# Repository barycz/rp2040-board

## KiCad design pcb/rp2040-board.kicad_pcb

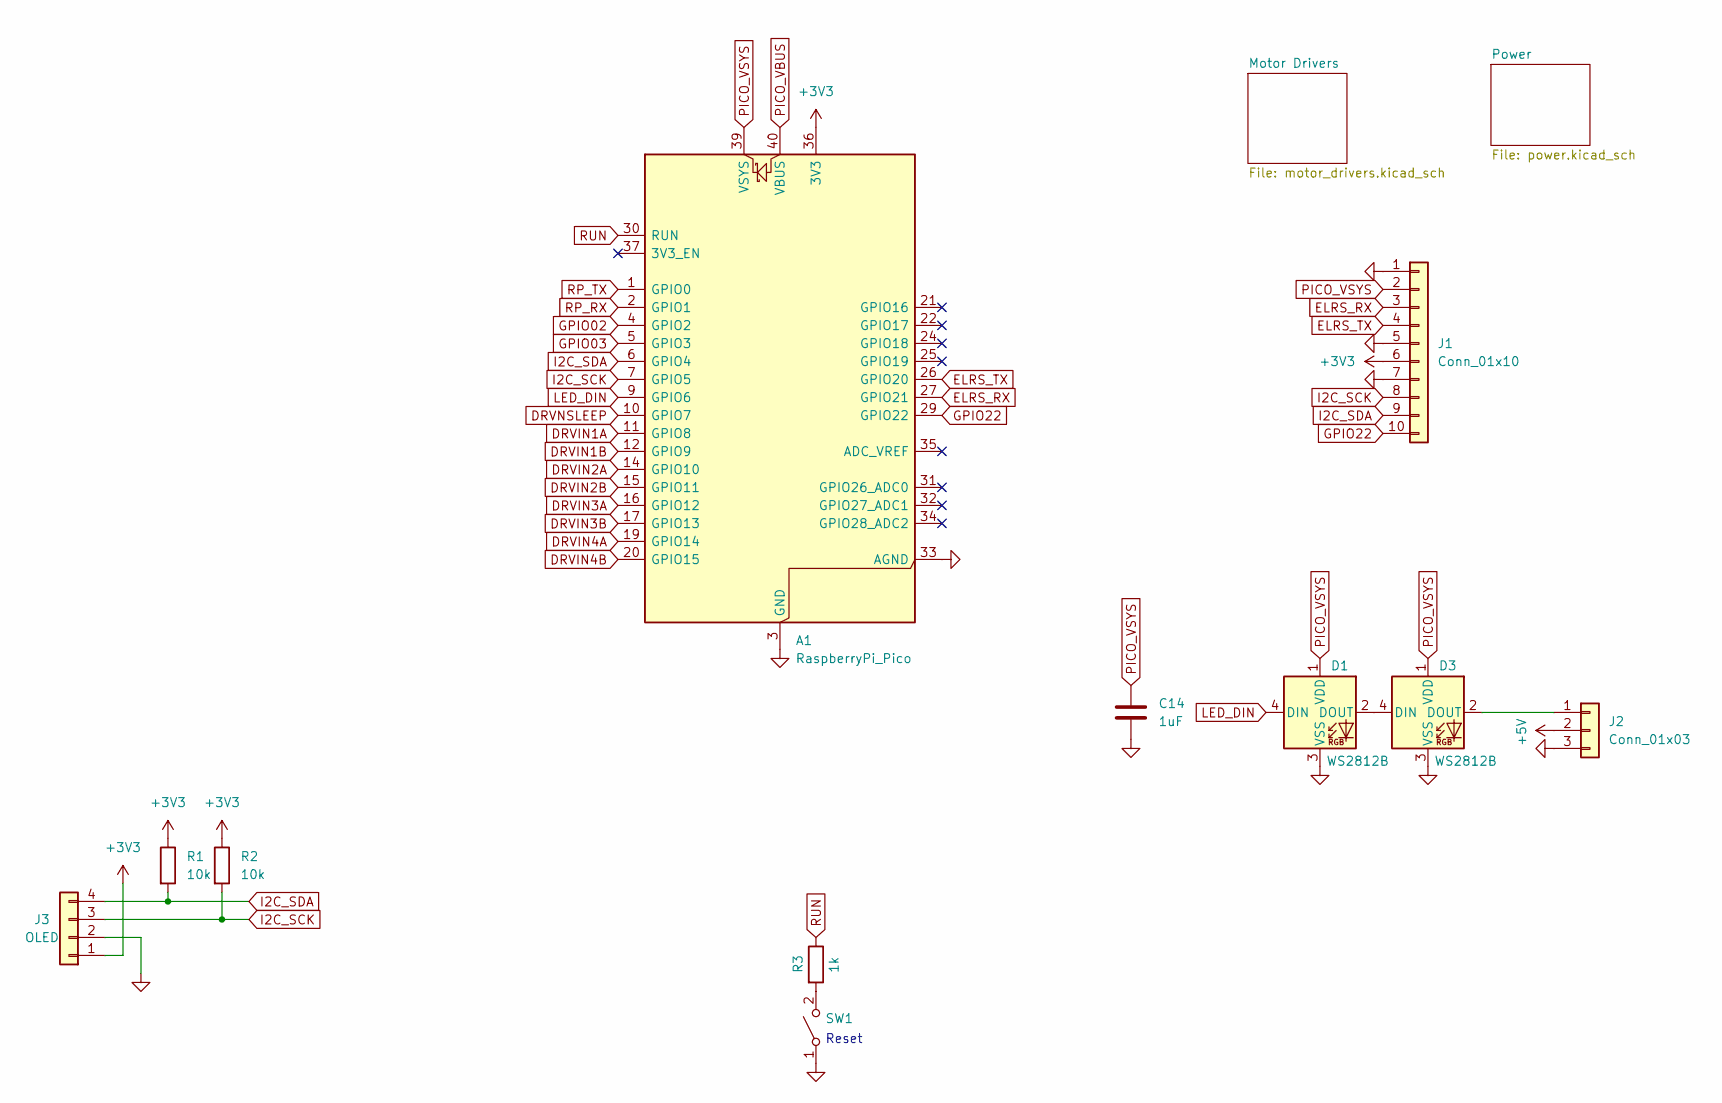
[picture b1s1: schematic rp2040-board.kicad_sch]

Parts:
A1: RaspberryPi_Pico; RaspberryPi_Pico_Common_SMD
C14: 1uF; C_0805_2012Metric; LCSC Part C28323
D1, D3: WS2812B; LED_WS2812B_PLCC4_5.0x5.0mm_P3.2mm; LCSC Part C42417498
J1: Conn_01x10; PinHeader_1x10_P2.54mm_Vertical
J2: Conn_01x03; PinHeader_1x03_P2.54mm_Vertical
J3: OLED; i2c oled display 0.96 inch VCC GND; JLCPCB BOM false
R1, R2: 10k; R_0402_1005Metric; LCSC Part C25744
R3: 1k; R_0402_1005Metric; LCSC Part C11702
SW1: TS-1187A-B-A-B; SW_Push_1P1T_XKB_TS-1187A; LCSC Part C318884

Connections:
+3V3: A1.36 (3V3), J1.6, J3.1, R1.1, R2.1; also elsewhere on the board
+5V: J2.2; also elsewhere on the board
DRVIN1A: A1.11 (GPIO8); also elsewhere on the board
DRVIN1B: A1.12 (GPIO9); also elsewhere on the board
DRVIN2A: A1.14 (GPIO10); also elsewhere on the board
DRVIN2B: A1.15 (GPIO11); also elsewhere on the board
DRVIN3A: A1.16 (GPIO12); also elsewhere on the board
DRVIN3B: A1.17 (GPIO13); also elsewhere on the board
DRVIN4A: A1.19 (GPIO14); also elsewhere on the board
DRVIN4B: A1.20 (GPIO15); also elsewhere on the board
DRVNSLEEP: A1.10 (GPIO7); also elsewhere on the board
ELRS_RX: A1.27 (GPIO21), J1.3
ELRS_TX: A1.26 (GPIO20), J1.4
GND: A1.3 (GND), A1.8 (GND), A1.13 (GND), A1.18 (GND), A1.23 (GND), A1.28 (GND), A1.33 (AGND), A1.38 (GND), C14.2, D1.3 (VSS), D3.3 (VSS), J1.1, J1.5, J1.7, J2.3, J3.2, SW1.1 (A); also elsewhere on the board
GPIO02: A1.4 (GPIO2); also elsewhere on the board
GPIO03: A1.5 (GPIO3); also elsewhere on the board
GPIO22: A1.29 (GPIO22), J1.10
I2C_SCK: A1.7 (GPIO5), J1.8, J3.3, R2.2; also elsewhere on the board
I2C_SDA: A1.6 (GPIO4), J1.9, J3.4, R1.2; also elsewhere on the board
LED_DIN: A1.9 (GPIO6), D1.4 (DIN)
unnamed: D1.2 (DOUT), D3.4 (DIN)
unnamed: D3.2 (DOUT), J2.1
unnamed: R3.2, SW1.2 (B)
PICO_VBUS: A1.40 (VBUS); also elsewhere on the board
PICO_VSYS: A1.39 (VSYS), C14.1, D1.1 (VDD), D3.1 (VDD), J1.2; also elsewhere on the board
RP_RX: A1.2 (GPIO1); also elsewhere on the board
RP_TX: A1.1 (GPIO0); also elsewhere on the board
RUN: A1.30 (RUN), R3.1

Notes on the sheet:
Reset

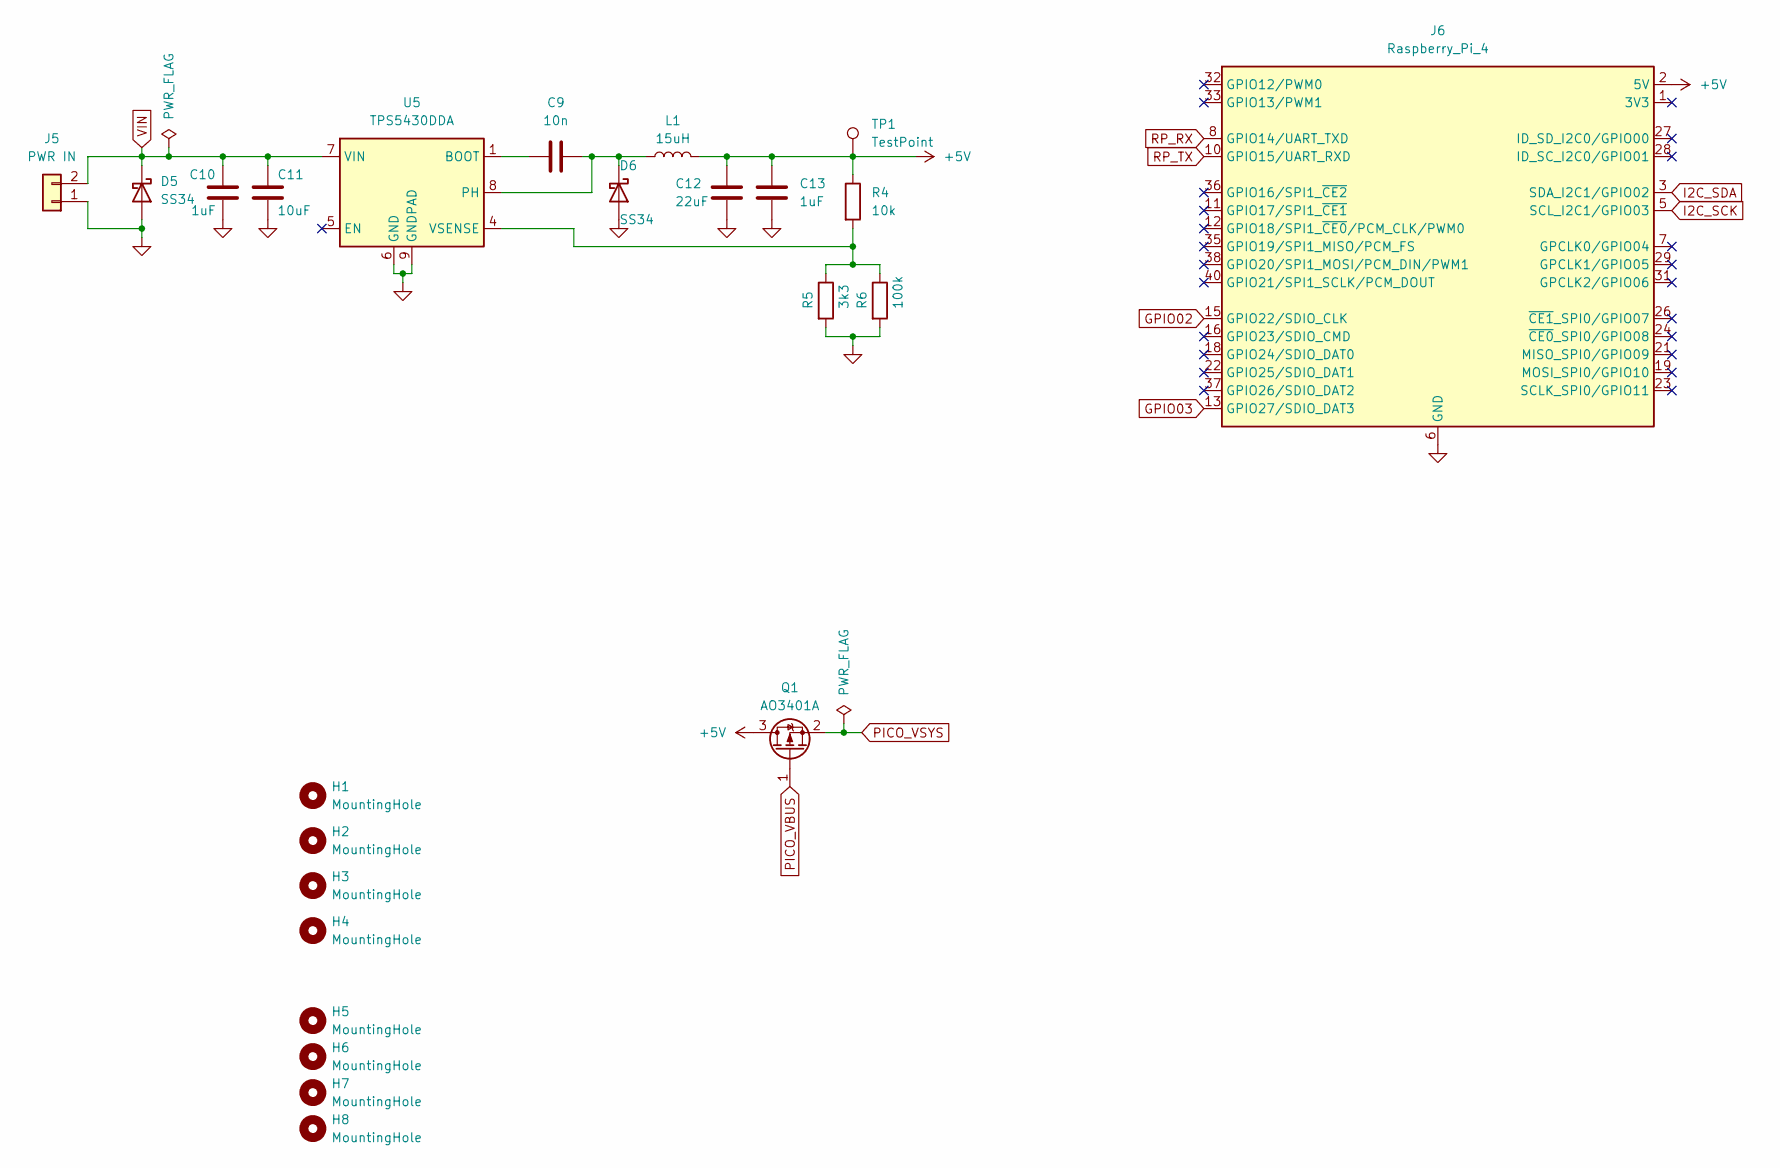
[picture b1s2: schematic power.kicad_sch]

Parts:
C9: 10n; C_0402_1005Metric; LCSC Part C15195
C10, C13: 1uF; C_0805_2012Metric; LCSC Part C28323
C11: 10uF; C_0805_2012Metric; LCSC Part C440198
C12: 22uF; C_0805_2012Metric; LCSC Part C45783
D5, D6: SS34; D_SMA; LCSC Part C8678
H1, H2, H3, H4: MountingHole; MountingHole_2.7mm
H5, H6, H7, H8: MountingHole; MountingHole_2.2mm_M2
J5: PWR IN; AMASS_XT30U-M_1x02_P5.0mm_Vertical
J6: Raspberry_Pi_4; PinSocket_2x10_P2.54mm_Vertical
L1: 15uH; L_Changjiang_FXL0630; LCSC Part C177243
Q1: AO3401A; SOT-23; LCSC Part C15127
R4: 10k; R_0402_1005Metric; LCSC Part C25744
R5: 3k3; R_0402_1005Metric; LCSC Part C25890
R6: 100k; R_0402_1005Metric; LCSC Part C25741
TP1: TestPoint; TestPoint_Pad_D1.0mm
U5: TPS5430DDA; TI_SO-PowerPAD-8_ThermalVias; LCSC Part C9864

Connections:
+5V: C12.1, C13.1, J6.2 (5V), J6.4 (5V), L1.2, Q1.3 (D), R4.1, TP1.1; also elsewhere on the board
GND: C10.2, C11.2, C12.2, C13.2, D5.2 (A), D6.2 (A), J5.1, J6.6 (GND), J6.9 (GND), J6.14 (GND), J6.20 (GND), J6.25 (GND), J6.30 (GND), J6.34 (GND), J6.39 (GND), R5.2, R6.2, U5.6 (GND), U5.9 (GNDPAD); also elsewhere on the board
GPIO02: J6.15 (GPIO22/SDIO_CLK); also elsewhere on the board
GPIO03: J6.13 (GPIO27/SDIO_DAT3); also elsewhere on the board
I2C_SCK: J6.5 (SCL_I2C1/GPIO03); also elsewhere on the board
I2C_SDA: J6.3 (SDA_I2C1/GPIO02); also elsewhere on the board
unnamed: C9.2, D6.1 (K), L1.1, U5.8 (PH)
unnamed: C9.1, U5.1 (BOOT)
unnamed: R4.2, R5.1, R6.1, U5.4 (VSENSE)
PICO_VBUS: Q1.1 (G); also elsewhere on the board
PICO_VSYS: Q1.2 (S); also elsewhere on the board
RP_RX: J6.8 (GPIO14/UART_TXD); also elsewhere on the board
RP_TX: J6.10 (GPIO15/UART_RXD); also elsewhere on the board
VIN: C10.1, C11.1, D5.1 (K), J5.2, U5.7 (VIN)

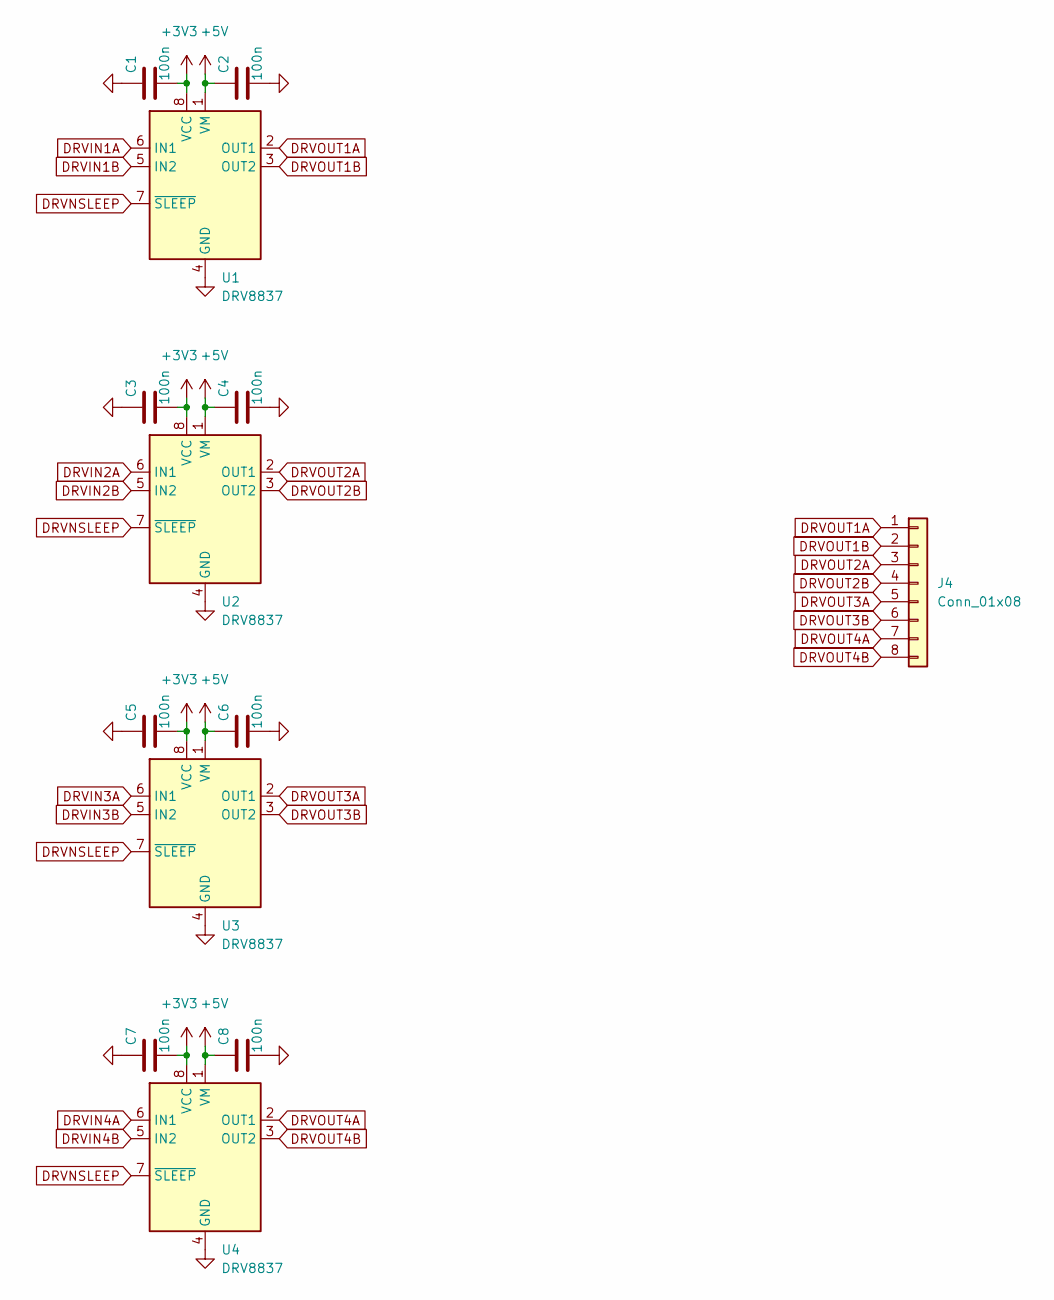
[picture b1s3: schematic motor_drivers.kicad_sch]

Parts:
C1, C2, C3, C4, C5, C6, C7, C8: 100n; C_0402_1005Metric; LCSC Part C1525
J4: Conn_01x08; PinHeader_1x08_P2.54mm_Vertical
U1, U2, U3, U4: DRV8837; WSON-8-1EP_2x2mm_P0.5mm_EP0.9x1.6mm; LCSC Part C39159

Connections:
+3V3: C1.2, C3.2, C5.2, C7.2, U1.8 (VCC), U2.8 (VCC), U3.8 (VCC), U4.8 (VCC); also elsewhere on the board
+5V: C2.1, C4.1, C6.1, C8.1, U1.1 (VM), U2.1 (VM), U3.1 (VM), U4.1 (VM); also elsewhere on the board
DRVIN1A: U1.6 (IN1); also elsewhere on the board
DRVIN1B: U1.5 (IN2); also elsewhere on the board
DRVIN2A: U2.6 (IN1); also elsewhere on the board
DRVIN2B: U2.5 (IN2); also elsewhere on the board
DRVIN3A: U3.6 (IN1); also elsewhere on the board
DRVIN3B: U3.5 (IN2); also elsewhere on the board
DRVIN4A: U4.6 (IN1); also elsewhere on the board
DRVIN4B: U4.5 (IN2); also elsewhere on the board
DRVNSLEEP: U1.7 (~SLEEP), U2.7 (~SLEEP), U3.7 (~SLEEP), U4.7 (~SLEEP); also elsewhere on the board
DRVOUT1A: J4.1, U1.2 (OUT1)
DRVOUT1B: J4.2, U1.3 (OUT2)
DRVOUT2A: J4.3, U2.2 (OUT1)
DRVOUT2B: J4.4, U2.3 (OUT2)
DRVOUT3A: J4.5, U3.2 (OUT1)
DRVOUT3B: J4.6, U3.3 (OUT2)
DRVOUT4A: J4.7, U4.2 (OUT1)
DRVOUT4B: J4.8, U4.3 (OUT2)
GND: C1.1, C2.2, C3.1, C4.2, C5.1, C6.2, C7.1, C8.2, U1.4 (GND), U1.9 (GND), U2.4 (GND), U2.9 (GND), U3.4 (GND), U3.9 (GND), U4.4 (GND), U4.9 (GND); also elsewhere on the board

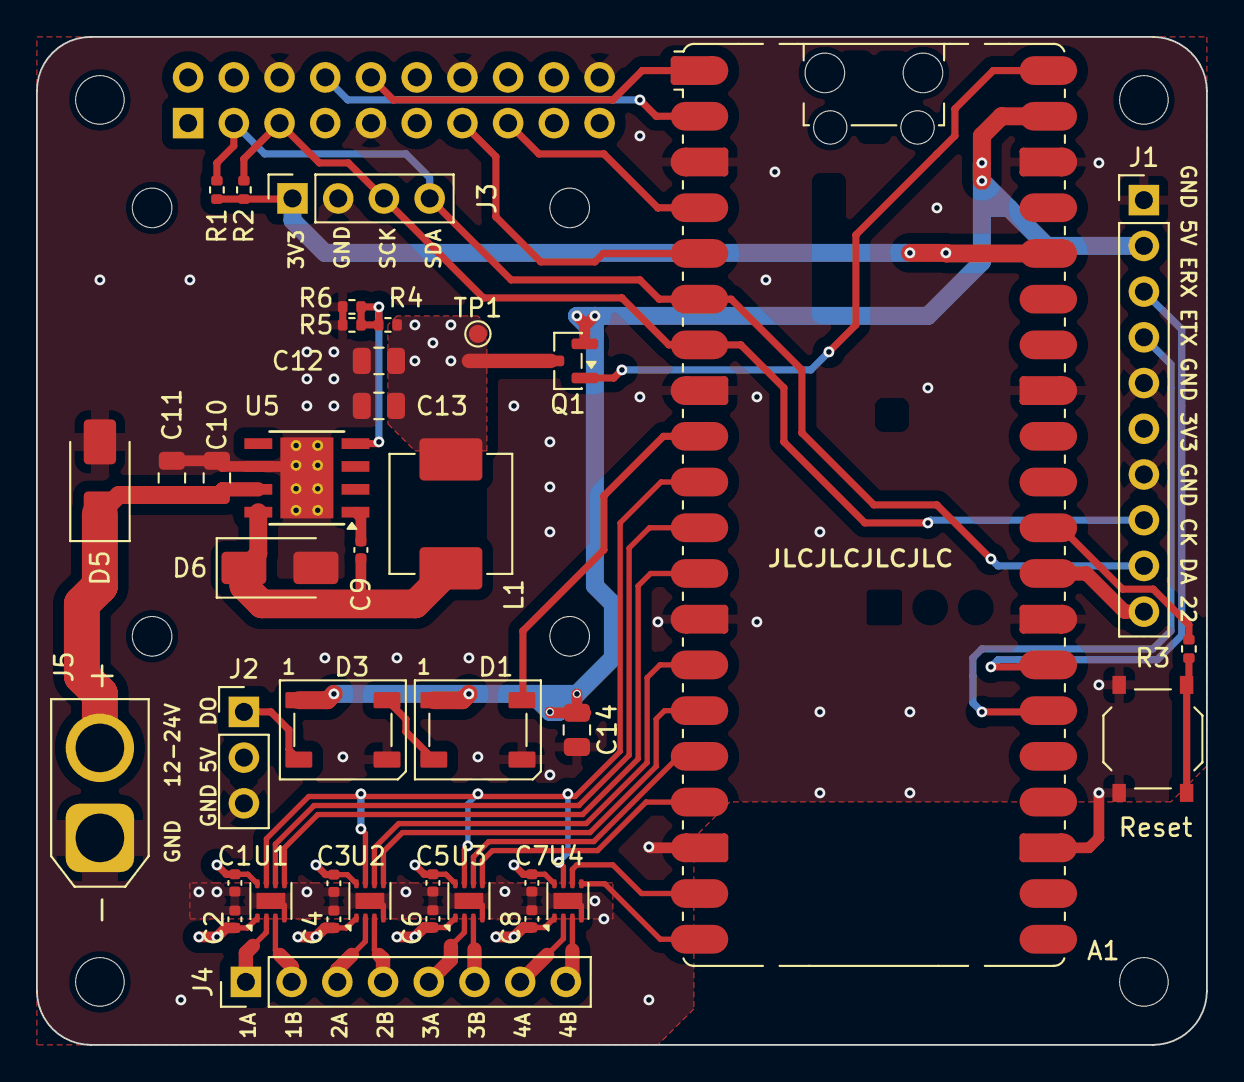
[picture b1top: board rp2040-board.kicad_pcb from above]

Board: 4 copper layers, 65.0 x 56.0 mm, 48 parts (1 on the bottom side), 40 nets.

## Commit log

2024-01-31 initial datasheets
2024-02-05 add initial hello world app, update .gitignore
2024-02-10 initial parts for bom generation
2024-02-10 add more parts to the BOM
2024-02-10 add SDK manual/getting started guide
2024-02-11 schematic wip
2024-02-13 schematic finalization, pcb draft
2024-02-14 pcb wip
2024-02-14 board wip
2024-02-17 board rc1
2024-02-17 board rc2
2024-02-17 board rc3
2024-02-17 add more datasheets
2024-02-18 board rc4, BOM cleanup
2024-02-18 enlarge power supply caps
2024-02-19 fixed pin assignment issues
2024-02-21 pin assignment issues fixed
2024-02-23 board rc5
2024-02-23 fabrication tweaks
2024-02-24 xtal capacitance closer to the target
2024-02-24 fixed via size
2024-02-24 last changes before fab
2024-02-25 files sent to fab
2024-03-05 testing app for DMX/RS485
2024-03-10 switched to pico sdk, display hellow world
2024-03-11 demo the rest of the board
2024-03-13 steal rotary/quadrature encoder example
2024-03-20 add dmx and display demo
2024-03-23 tidy up the main loop and measure performance
2024-03-23 WIP dmx512 pio sm
2024-03-24 use side set, use pio instead of uart
2024-03-26 nice bar to indicate channel value
2024-06-07 initial joystick app
2024-06-08 add basic joystick to midi app
2024-06-08 move/rename dmx controller app
2024-06-11 add support for simultanous midi and usb stdio
2024-06-12 add hard-coded calibration
2024-08-12 added initial crsf to midi transport
2024-08-20 move towards generic crsf to midi CC mapping
2025-03-14 app skeleton for the swing controller
2025-03-15 read MPU6050 data, filter and dump it
2025-03-15 swing phase detection
2025-03-16 simple pwm test code added
2025-03-16 first working implementation of the propeller
2025-03-19 second working implementation
2025-04-05 better pulse shape sent using dma
2025-04-08 add more propeller pulse waveforms
2025-04-13 more pulse waveforms
2025-04-20 more funky waveforms
2025-05-21 introduce random waveforms
2025-05-22 generate infinite random sequence
2025-07-19 rename crsf-to-midi as we are going to generalize it
2025-07-19 move the CRServoF library to the lib folder
2025-07-19 lost change from the previous commit
2025-07-20 demo crsf motor pwm
2025-07-22 simple mixing matrix for a 4-wheel mecanum car
2025-07-24 enlarged deadzone and asserts
2025-09-27 WIP on the second PCB, also resaved with kicad 9
2025-09-28 add motor drivers and split the schematic
2025-11-01 WIP on the power section of the new board
2025-11-02 WIP on the motor driver board
2025-11-02 wip on pcb
2025-11-05 wip on the pcb
2025-11-08 pcb almost done
2025-11-08 board final touches
2025-11-10 board rc4
2025-12-27 migrate to sdk 2.2.0 using the pico vs code extension
2025-12-29 update the crsf bridge app to work with the new board
